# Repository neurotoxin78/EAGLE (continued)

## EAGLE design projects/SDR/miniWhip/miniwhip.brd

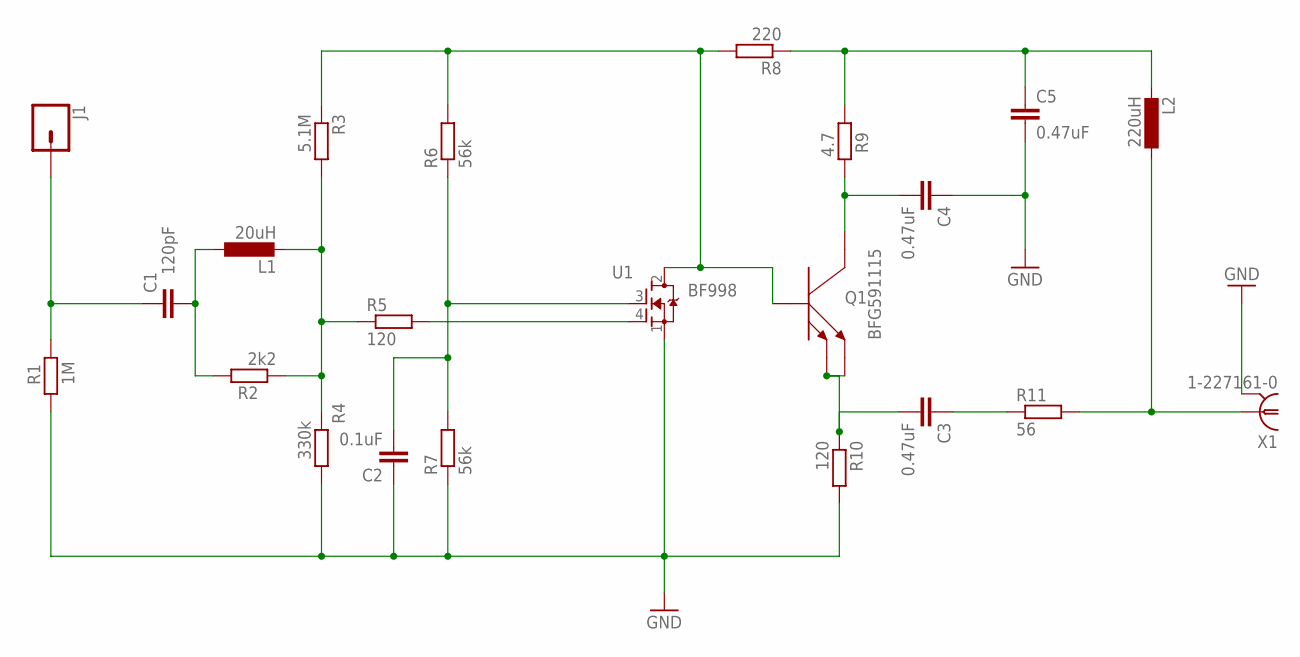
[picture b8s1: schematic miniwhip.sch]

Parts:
C1: 120pF; C0805
C2: 0.1uF; C0805K
C3, C4, C5: 0.47uF; C0805K
J1: CONN_01PTH_2MM; 1X01_2MM
L1: 20uH; L1812
L2: 220uH; 0204/7
Q1: BFG591115; SOT230P700X180-4N
R1: 1M; M0805
R2: 2k2; M0805
R3: 5.1M; 0207/10
R4: 330k; M0805
R5, R10: 120; M0805
R6, R7: 56k; M0805
R8: 220; M0805
R9: 4.7; M0805
R11: 56; M0805
U1: BF998; SOT190P230X110-4N
X1: 1-227161-0; AMP_227161

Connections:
GND: C2.1, C4.1, C5.2, R1.1, R4.2, R7.1, R10.2, U1.1 (S), X1.2
unnamed: C1.1, J1.1, R1.2
unnamed: C1.2, L1.1, R2.2
unnamed: L1.2, R2.1, R3.2, R4.1, R5.1
unnamed: R5.2, U1.4 (G1)
unnamed: C2.2, R6.1, R7.2, U1.3 (G)
unnamed: C3.2, Q1.1 (E1), Q1.3 (E2), R10.1
unnamed: L2.1, R11.2, X1.1
unnamed: Q1.2 (B), R3.1, R6.2, R8.2, U1.2 (D)
unnamed: C4.2, Q1.4 (C), R9.2
unnamed: C5.1, L2.2, R8.1, R9.1
unnamed: C3.1, R11.1

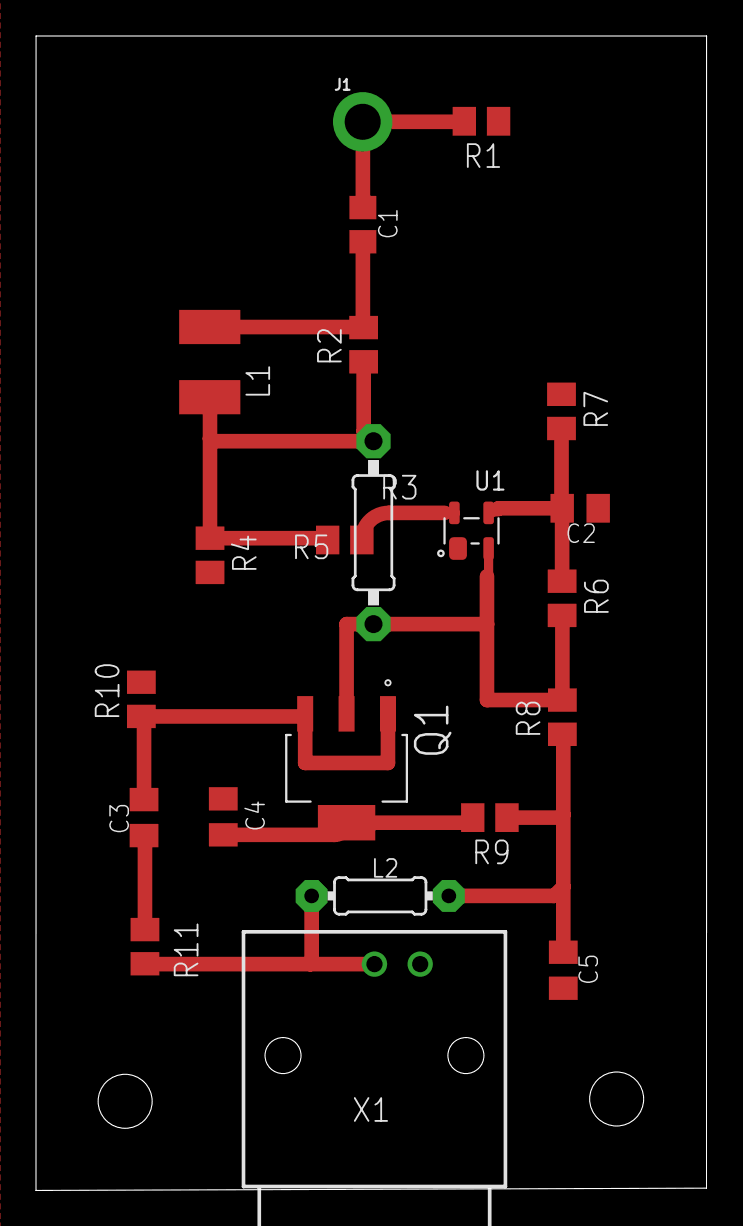
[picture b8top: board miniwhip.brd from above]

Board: 2 copper layers, 37.3 x 64.1 mm, 22 parts (0 on the bottom side), 12 nets.
